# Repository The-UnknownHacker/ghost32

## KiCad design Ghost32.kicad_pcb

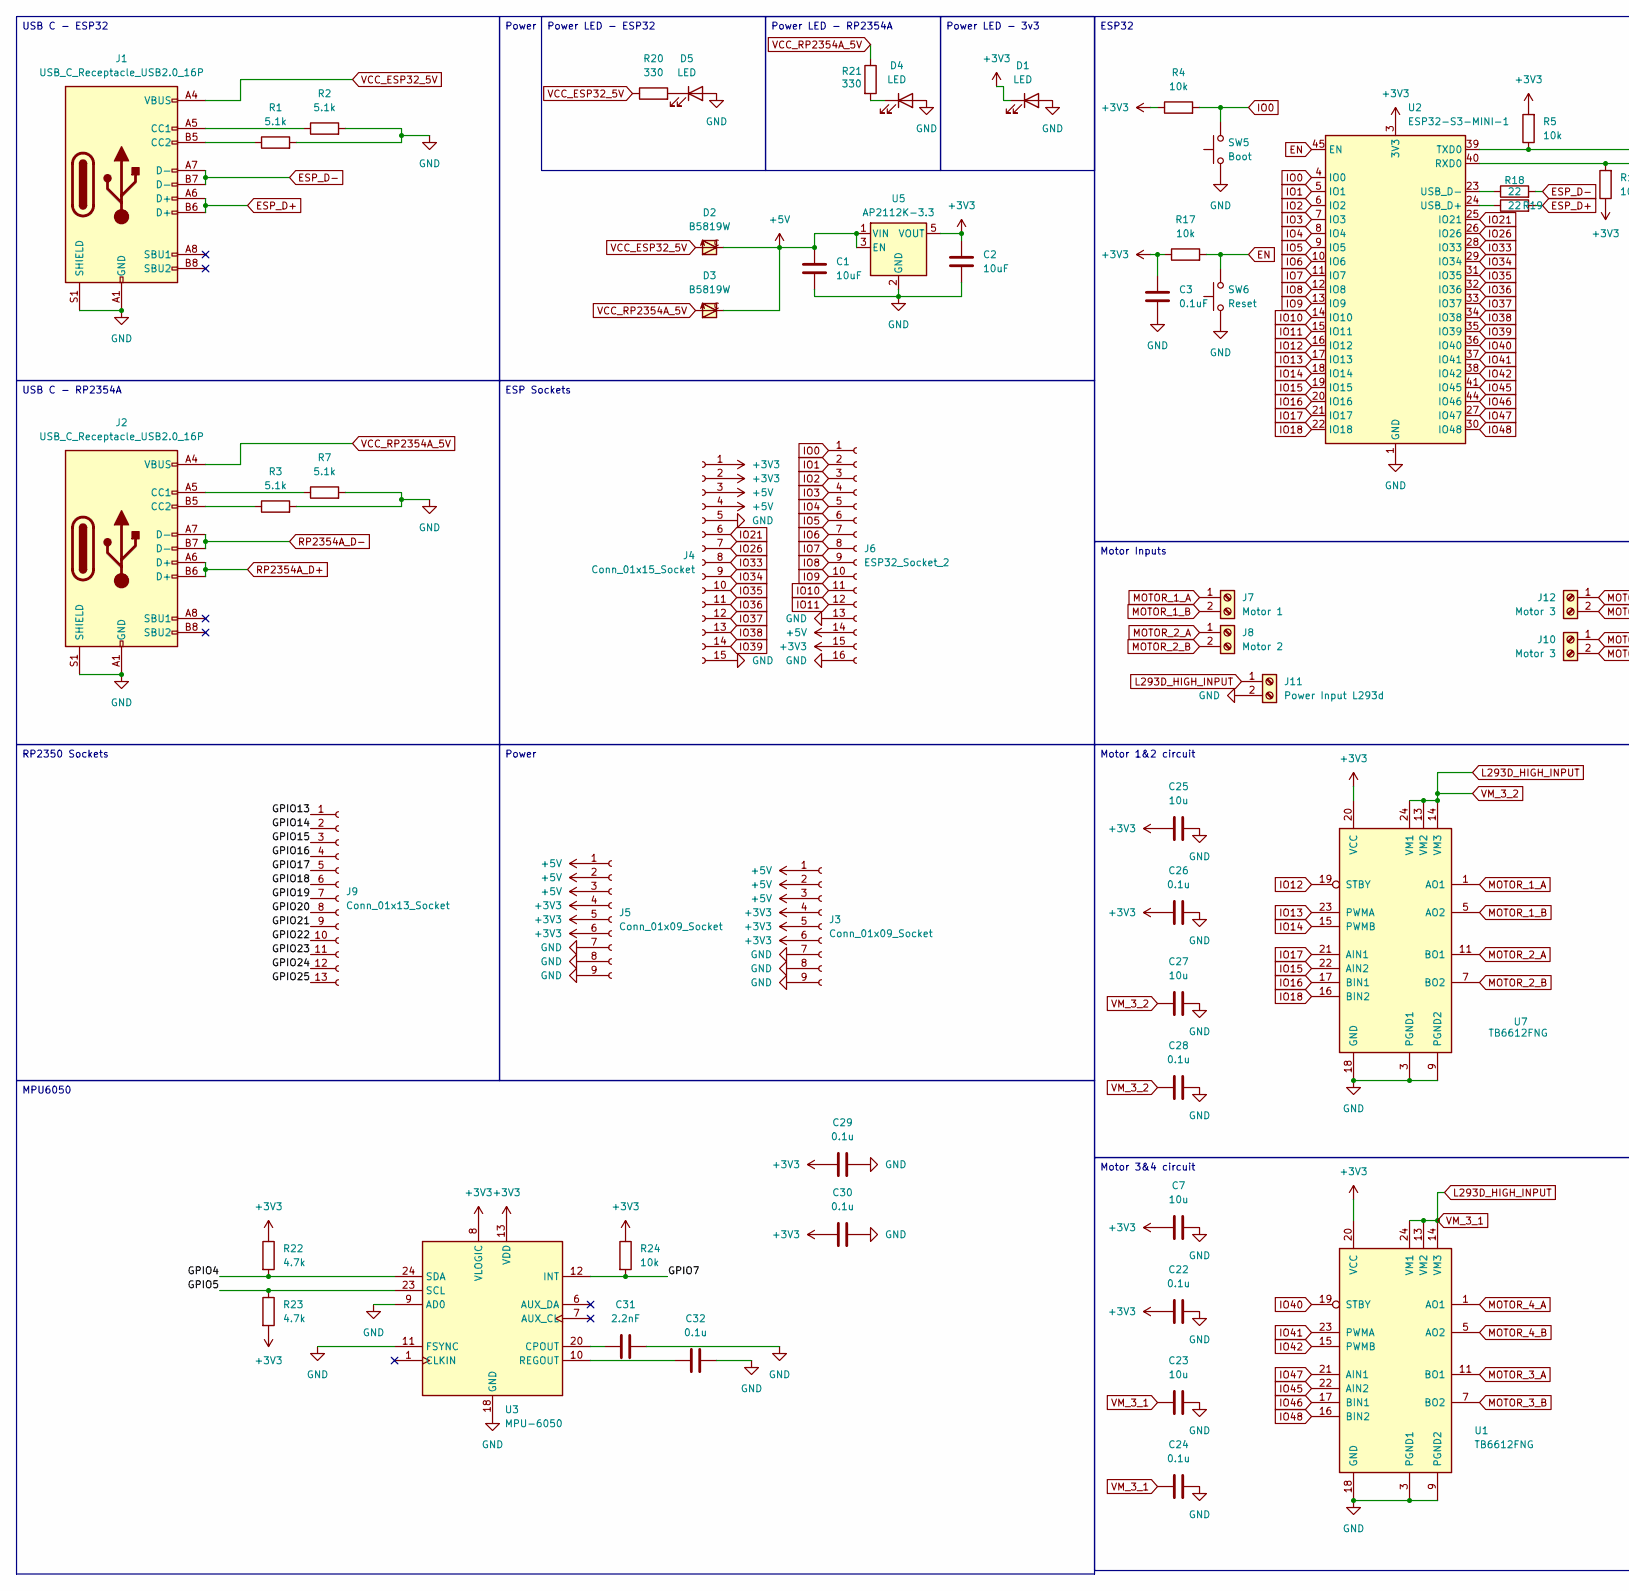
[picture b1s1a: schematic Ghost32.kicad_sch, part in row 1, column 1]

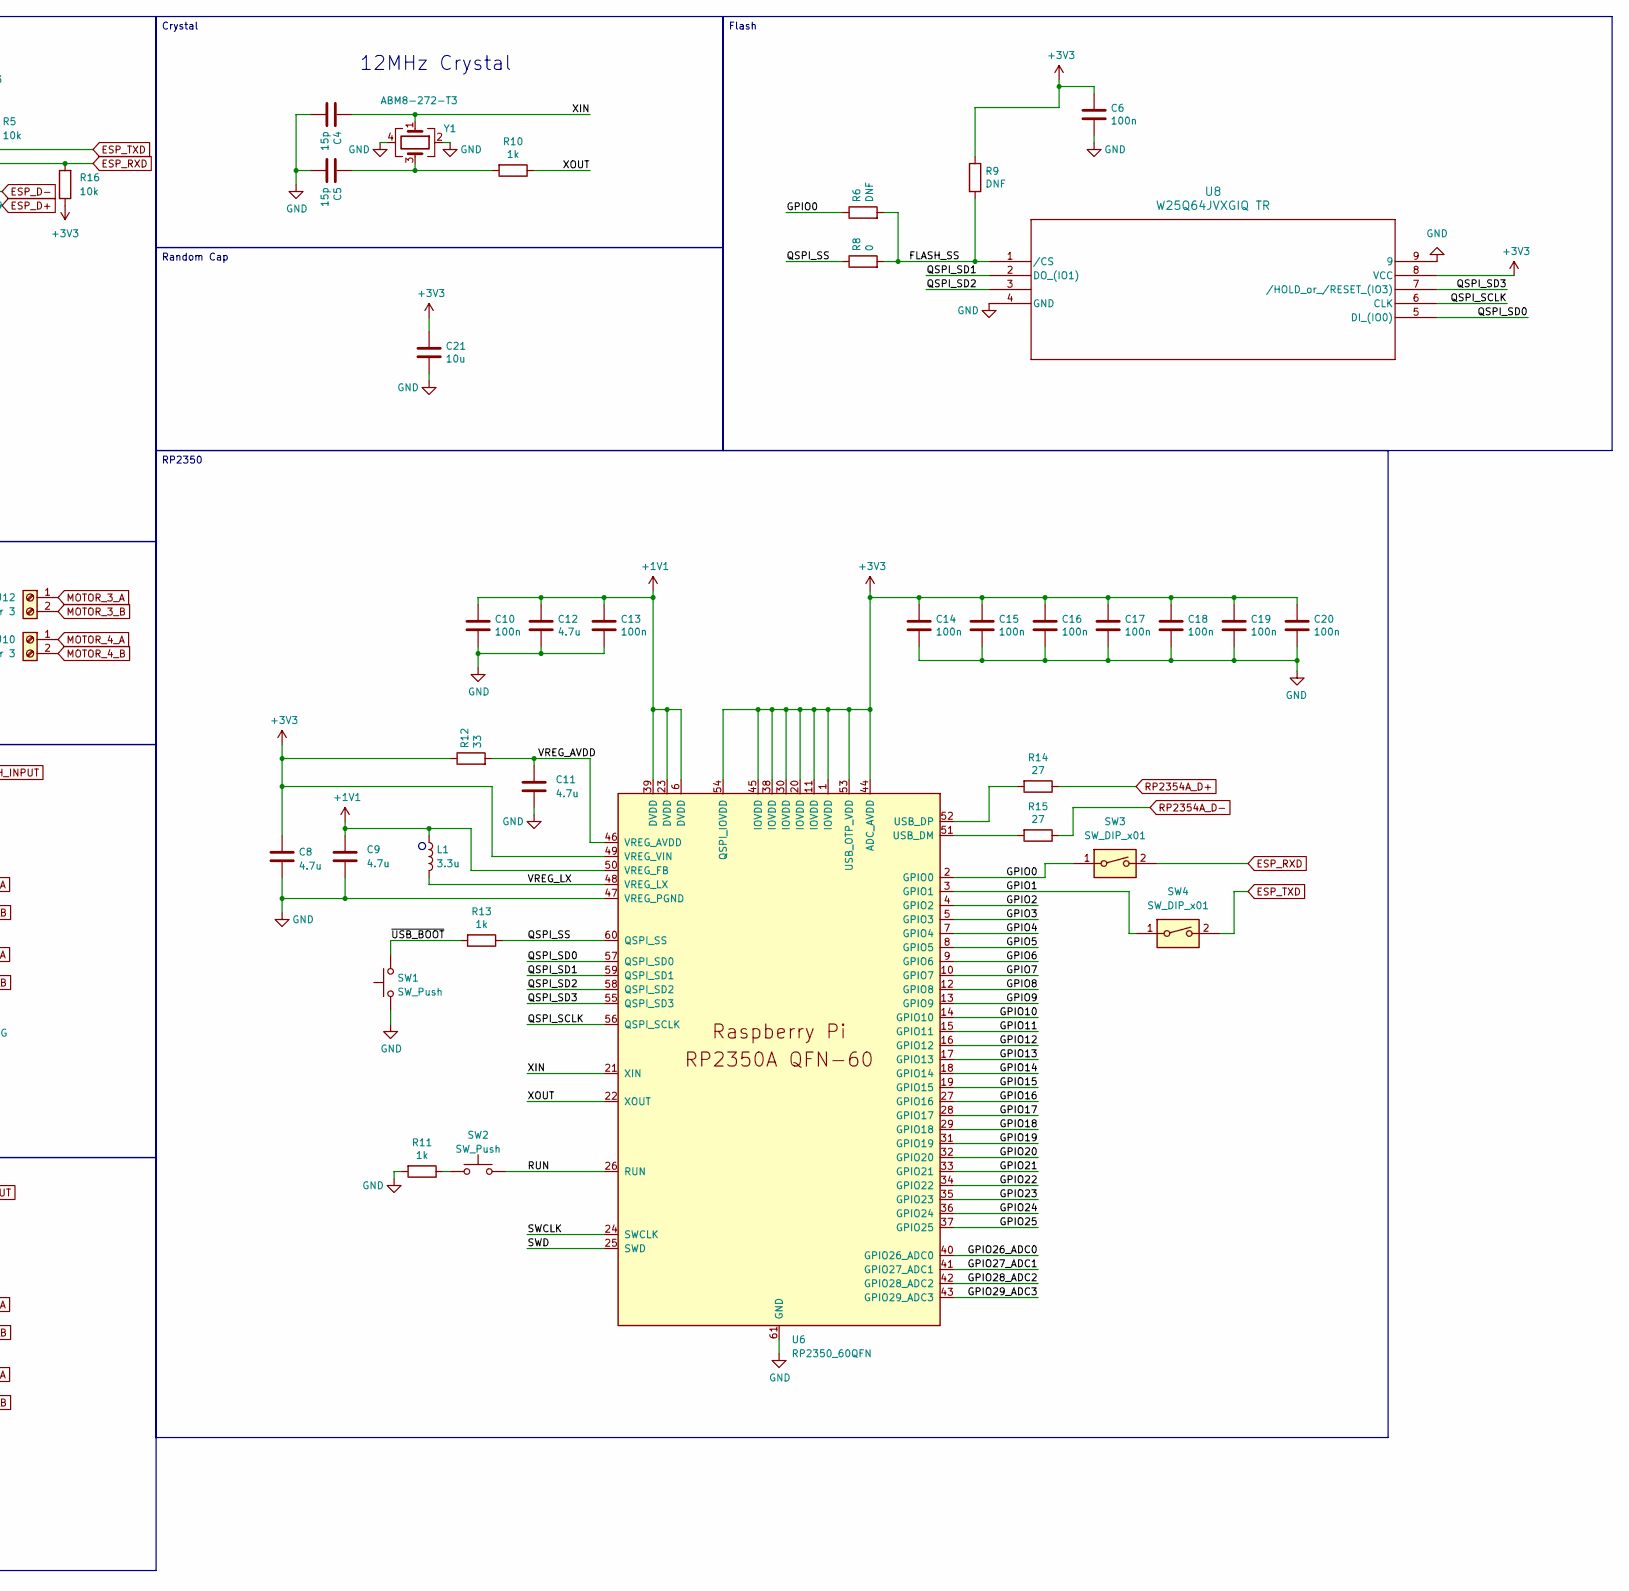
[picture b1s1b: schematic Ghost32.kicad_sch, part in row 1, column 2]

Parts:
C1, C2: 10uF; C_0402_1005Metric
C3: 0.1uF; C_0402_1005Metric
C4, C5: 15p; C_0402_1005Metric
C6, C10, C13, C14, C15, C16, C17, C18, C19, C20: 100n; C_0402_1005Metric
C7, C21, C23, C25, C27: 10u; C_0402_1005Metric
C8, C9, C11, C12: 4.7u; C_0402_1005Metric
C22, C24, C26, C28, C29, C30, C32: 0.1u; C_0402_1005Metric
C31: 2.2nF; C_0402_1005Metric
D1, D4, D5: LED; LED_0805_2012Metric
D2, D3: B5819W; SOD123FL
J1, J2: USB_C_Receptacle_USB2.0_16P; USB_C_Receptacle_HRO_TYPE-C-31-M-12
J3, J5: Conn_01x09_Socket; PinSocket_1x09_P2.54mm_Vertical
J4: Conn_01x15_Socket; PinSocket_1x15_P2.54mm_Vertical
J6: ESP32_Socket_2; PinSocket_1x16_P2.54mm_Vertical
J7: Motor 1; Altech_AK300_1x02_P5.00mm_45-Degree
J8: Motor 2; Altech_AK300_1x02_P5.00mm_45-Degree
J9: Conn_01x13_Socket; PinSocket_1x13_P2.54mm_Vertical
J10, J12: Motor 3; Altech_AK300_1x02_P5.00mm_45-Degree
J11: Power Input L293d; Altech_AK300_1x02_P5.00mm_45-Degree
L1: 3.3u; L_0805_2012Metric
R1, R2, R3, R7: 5.1k; R_0402_1005Metric
R4, R5, R16, R17, R24: 10k; R_0402_1005Metric
R6, R9: DNF; R_0402_1005Metric
R8: 0; R_0402_1005Metric
R10, R11, R13: 1k; R_0402_1005Metric
R12: 33; R_0402_1005Metric
R14, R15: 27; R_0402_1005Metric
R18, R19: 22; R_0402_1005Metric
R20, R21: 330; R_0402_1005Metric
R22, R23: 4.7k; R_0402_1005Metric
SW1, SW2: SW_Push; SW_Push_1P1T_NO_Vertical_Wuerth_434133025816
SW3, SW4: SW_DIP_x01; SW_DIP_SPSTx01_Slide_6.7x4.1mm_W6.73mm_P2.54mm_LowProfile_J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
SW5: Boot; SW_Push_1P1T_NO_Vertical_Wuerth_434133025816
SW6: Reset; SW_Push_1P1T_NO_Vertical_Wuerth_434133025816
U1, U7: TB6612FNG; SSOP-24_5.3x8.2mm_P0.65mm
U2: ESP32-S3-MINI-1; ESP32-S2-MINI-1
U3: MPU-6050; InvenSense_QFN-24_4x4mm_P0.5mm
U5: AP2112K-3.3; SOT-23-5
U6: RP2350_60QFN; QFN-60-1EP_7x7mm_P0.4mm_EP3.4x3.4mm
U8: W25Q64JVXGIQ TR; DFN_XGIQ TR_WIN
Y1: ABM8-272-T3; Crystal_SMD_3225-4Pin_3.2x2.5mm

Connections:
+1V1: C9.1, C10.1, C12.1, C13.1, L1.1, U6.6 (DVDD), U6.23 (DVDD), U6.39 (DVDD), U6.50 (VREG_FB)
+3V3: C2.1, C3.1, C6.1, C7.1, C8.1, C14.1, C15.1, C16.1, C17.1, C18.1, C19.1, C20.1, C21.1, C22.1, C25.1, C26.1, C29.1, C30.1, D1.1 (K), J3.4, J3.5, J3.6, J4.1, J4.2, J5.4, J5.5, J5.6, J6.15, R4.1, R5.2, R9.1, R12.1, R16.1, R17.1, R22.1, R23.2, R24.1, U1.20 (VCC), U2.3 (3V3), U3.8 (VLOGIC), U3.13 (VDD), U5.5 (VOUT), U6.1 (IOVDD), U6.11 (IOVDD), U6.20 (IOVDD), U6.30 (IOVDD), U6.38 (IOVDD), U6.44 (ADC_AVDD), U6.45 (IOVDD), U6.49 (VREG_VIN), U6.53 (USB_OTP_VDD), U6.54 (QSPI_IOVDD), U7.20 (VCC), U8.8 (VCC)
+5V: C1.1, D2.C, D3.C, J3.1, J3.2, J3.3, J4.3, J4.4, J5.1, J5.2, J5.3, J6.14, U5.1 (VIN), U5.3 (EN)
/FLASH_SS: R6.2, R8.2, R9.2, U8.1 (/CS)
/GPIO0: R6.1, SW3.1, U6.2 (GPIO0)
/GPIO1: SW4.1, U6.3 (GPIO1)
/GPIO2: U6.4 (GPIO2)
/GPIO3: U6.5 (GPIO3)
/GPIO4: R22.2, U3.24 (SDA), U6.7 (GPIO4)
/GPIO5: R23.1, U3.23 (SCL), U6.8 (GPIO5)
/GPIO6: U6.9 (GPIO6)
/GPIO7: R24.2, U3.12 (INT), U6.10 (GPIO7)
/GPIO8: U6.12 (GPIO8)
/GPIO9: U6.13 (GPIO9)
/GPIO10: U6.14 (GPIO10)
/GPIO11: U6.15 (GPIO11)
/GPIO12: U6.16 (GPIO12)
/GPIO13: J9.1, U6.17 (GPIO13)
/GPIO14: J9.2, U6.18 (GPIO14)
/GPIO15: J9.3, U6.19 (GPIO15)
/GPIO16: J9.4, U6.27 (GPIO16)
/GPIO17: J9.5, U6.28 (GPIO17)
/GPIO18: J9.6, U6.29 (GPIO18)
/GPIO19: J9.7, U6.31 (GPIO19)
/GPIO20: J9.8, U6.32 (GPIO20)
/GPIO21: J9.9, U6.33 (GPIO21)
/GPIO22: J9.10, U6.34 (GPIO22)
/GPIO23: J9.11, U6.35 (GPIO23)
/GPIO24: J9.12, U6.36 (GPIO24)
/GPIO25: J9.13, U6.37 (GPIO25)
/GPIO26_ADC0: U6.40 (GPIO26_ADC0)
/GPIO27_ADC1: U6.41 (GPIO27_ADC1)
/GPIO28_ADC2: U6.42 (GPIO28_ADC2)
/GPIO29_ADC3: U6.43 (GPIO29_ADC3)
/QSPI_SCLK: U6.56 (QSPI_SCLK), U8.6 (CLK)
/QSPI_SD0: U6.57 (QSPI_SD0), U8.5 (DI_(IO0))
/QSPI_SD1: U6.59 (QSPI_SD1), U8.2 (DO_(IO1))
/QSPI_SD2: U6.58 (QSPI_SD2), U8.3
/QSPI_SD3: U6.55 (QSPI_SD3), U8.7 (/HOLD_or_/RESET_(IO3))
/QSPI_SS: R8.1, R13.1, U6.60 (QSPI_SS)
/RUN: SW2.2, U6.26 (RUN)
/SWCLK: U6.24 (SWCLK)
/SWD: U6.25 (SWD)
/VREG_AVDD: C11.1, R12.2, U6.46 (VREG_AVDD)
/VREG_LX: L1.2, U6.48 (VREG_LX)
/XIN: C4.1, U6.21 (XIN), Y1.1
/XOUT: R10.1, U6.22 (XOUT)
/~USB_BOOT: R13.2, SW1.2
EN: R17.2, SW6.2, U2.45 (EN)
ESP_D+: J1.A6 (D+), J1.B6 (D+), R19.2
ESP_D-: J1.A7 (D-), J1.B7 (D-), R18.2
ESP_RXD: R16.2, SW3.2, U2.40 (RXD0)
ESP_TXD: R5.1, SW4.2, U2.39 (TXD0)
GND: C1.2, C2.2, C3.2, C4.2, C5.2, C6.2, C7.2, C8.2, C9.2, C10.2, C11.2, C12.2, C13.2, C14.2, C15.2, C16.2, C17.2, C18.2, C19.2, C20.2, C21.2, C22.2, C23.2, C24.2, C25.2, C26.2, C27.2, C28.2, C29.2, C30.2, C31.2, C32.2, D1.2 (A), D4.2 (A), D5.2 (A), J1.A1 (GND), J1.A12 (GND), J1.B1 (GND), J1.B12 (GND), J1.S1 (SHIELD), J2.A1 (GND), J2.A12 (GND), J2.B1 (GND), J2.B12 (GND), J2.S1 (SHIELD), J3.7, J3.8, J3.9, J4.5, J4.15, J5.7, J5.8, J5.9, J6.13, J6.16, J11.2, R1.2, R2.2, R3.2, R7.2, R11.2, SW1.1, SW5.1, SW6.1, U1.3 (PGND1), U1.4 (PGND1), U1.9 (PGND2), U1.10 (PGND2), U1.18 (GND), U2.1 (GND), U2.2 (GND), U2.42 (GND), U2.43 (GND), U2.46 (GND), U2.47 (GND), U2.48 (GND), U2.49 (GND), U2.50 (GND), U2.51 (GND), U2.52 (GND), U2.53 (GND), U2.54 (GND), U2.55 (GND), U2.56 (GND), U2.57 (GND), U2.58 (GND), U2.59 (GND), U2.60 (GND), U2.61 (GND), U2.62 (GND), U2.63 (GND), U2.64 (GND), U2.65 (GND), U3.9 (AD0), U3.11 (FSYNC), U3.18 (GND), U5.2 (GND), U6.47 (VREG_PGND), U6.61 (GND), U7.3 (PGND1), U7.4 (PGND1), U7.9 (PGND2), U7.10 (PGND2), U7.18 (GND), U8.4 (GND), U8.9, Y1.2, Y1.4
IO0: J6.1, R4.2, SW5.2, U2.4 (IO0)
IO1: J6.2, U2.5 (IO1)
IO2: J6.3, U2.6 (IO2)
IO3: J6.4, U2.7 (IO3)
IO4: J6.5, U2.8 (IO4)
IO5: J6.6, U2.9 (IO5)
IO6: J6.7, U2.10 (IO6)
IO7: J6.8, U2.11 (IO7)
IO8: J6.9, U2.12 (IO8)
IO9: J6.10, U2.13 (IO9)
IO10: J6.11, U2.14 (IO10)
IO11: J6.12, U2.15 (IO11)
IO12: U2.16 (IO12), U7.19 (STBY)
IO13: U2.17 (IO13), U7.23 (PWMA)
IO14: U2.18 (IO14), U7.15 (PWMB)
IO15: U2.19 (IO15), U7.22 (AIN2)
IO16: U2.20 (IO16), U7.17 (BIN1)
IO17: U2.21 (IO17), U7.21 (AIN1)
IO18: U2.22 (IO18), U7.16 (BIN2)
IO21: J4.6, U2.25 (IO21)
IO26: J4.7, U2.26 (IO26)
IO33: J4.8, U2.28 (IO33)
IO34: J4.9, U2.29 (IO34)
IO35: J4.10, U2.31 (IO35)
IO36: J4.11, U2.32 (IO36)
IO37: J4.12, U2.33 (IO37)
IO38: J4.13, U2.34 (IO38)
IO39: J4.14, U2.35 (IO39)
IO40: U1.19 (STBY), U2.36 (IO40)
IO41: U1.23 (PWMA), U2.37 (IO41)
IO42: U1.15 (PWMB), U2.38 (IO42)
IO45: U1.22 (AIN2), U2.41 (IO45)
IO46: U1.17 (BIN1), U2.44 (IO46)
IO47: U1.21 (AIN1), U2.27 (IO47)
IO48: U1.16 (BIN2), U2.30 (IO48)
L293D_HIGH_INPUT: C23.1, C24.1, C27.1, C28.1, J11.1, U1.13 (VM2), U1.14 (VM3), U1.24 (VM1), U7.13 (VM2), U7.14 (VM3), U7.24 (VM1)
MOTOR_1_A: J7.1, U7.1 (AO1), U7.2 (AO1)
MOTOR_1_B: J7.2, U7.5 (AO2), U7.6 (AO2)
MOTOR_2_A: J8.1, U7.11 (BO1), U7.12 (BO1)
MOTOR_2_B: J8.2, U7.7 (BO2), U7.8 (BO2)
MOTOR_3_A: J12.1, U1.11 (BO1), U1.12 (BO1)
MOTOR_3_B: J12.2, U1.7 (BO2), U1.8 (BO2)
MOTOR_4_A: J10.1, U1.1 (AO1), U1.2 (AO1)
MOTOR_4_B: J10.2, U1.5 (AO2), U1.6 (AO2)
unnamed: C5.1, R10.2, Y1.3
unnamed: D4.1 (K), R21.2
unnamed: D5.1 (K), R20.2
unnamed: J1.A5 (CC1), R2.1
unnamed: J1.B5 (CC2), R1.1
unnamed: J2.A5 (CC1), R7.1
unnamed: J2.B5 (CC2), R3.1
unnamed: R11.1, SW2.1
unnamed: R19.1, U2.24 (USB_D+)
unnamed: R18.1, U2.23 (USB_D-)
unnamed: C31.1, U3.20 (CPOUT)
unnamed: C32.1, U3.10 (REGOUT)
unnamed: R15.2, U6.51 (USB_DM)
unnamed: R14.2, U6.52 (USB_DP)
RP2354A_D+: J2.A6 (D+), J2.B6 (D+), R14.1
RP2354A_D-: J2.A7 (D-), J2.B7 (D-), R15.1
VCC_ESP32_5V: D2.A, J1.A4 (VBUS), J1.A9 (VBUS), J1.B4 (VBUS), J1.B9 (VBUS), R20.1
VCC_RP2354A_5V: D3.A, J2.A4 (VBUS), J2.A9 (VBUS), J2.B4 (VBUS), J2.B9 (VBUS), R21.1

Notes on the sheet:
12MHz Crystal
Motor Inputs
ESP32
Power LED - RP2354A
Flash
Power
USB C - ESP32
Power
Power LED - ESP32
Random Cap
Crystal
Power LED - 3v3
MPU6050
ESP Sockets
RP2350 Sockets
Motor 1&2 circuit
USB C - RP2354A
RP2350
Motor 3&4 circuit

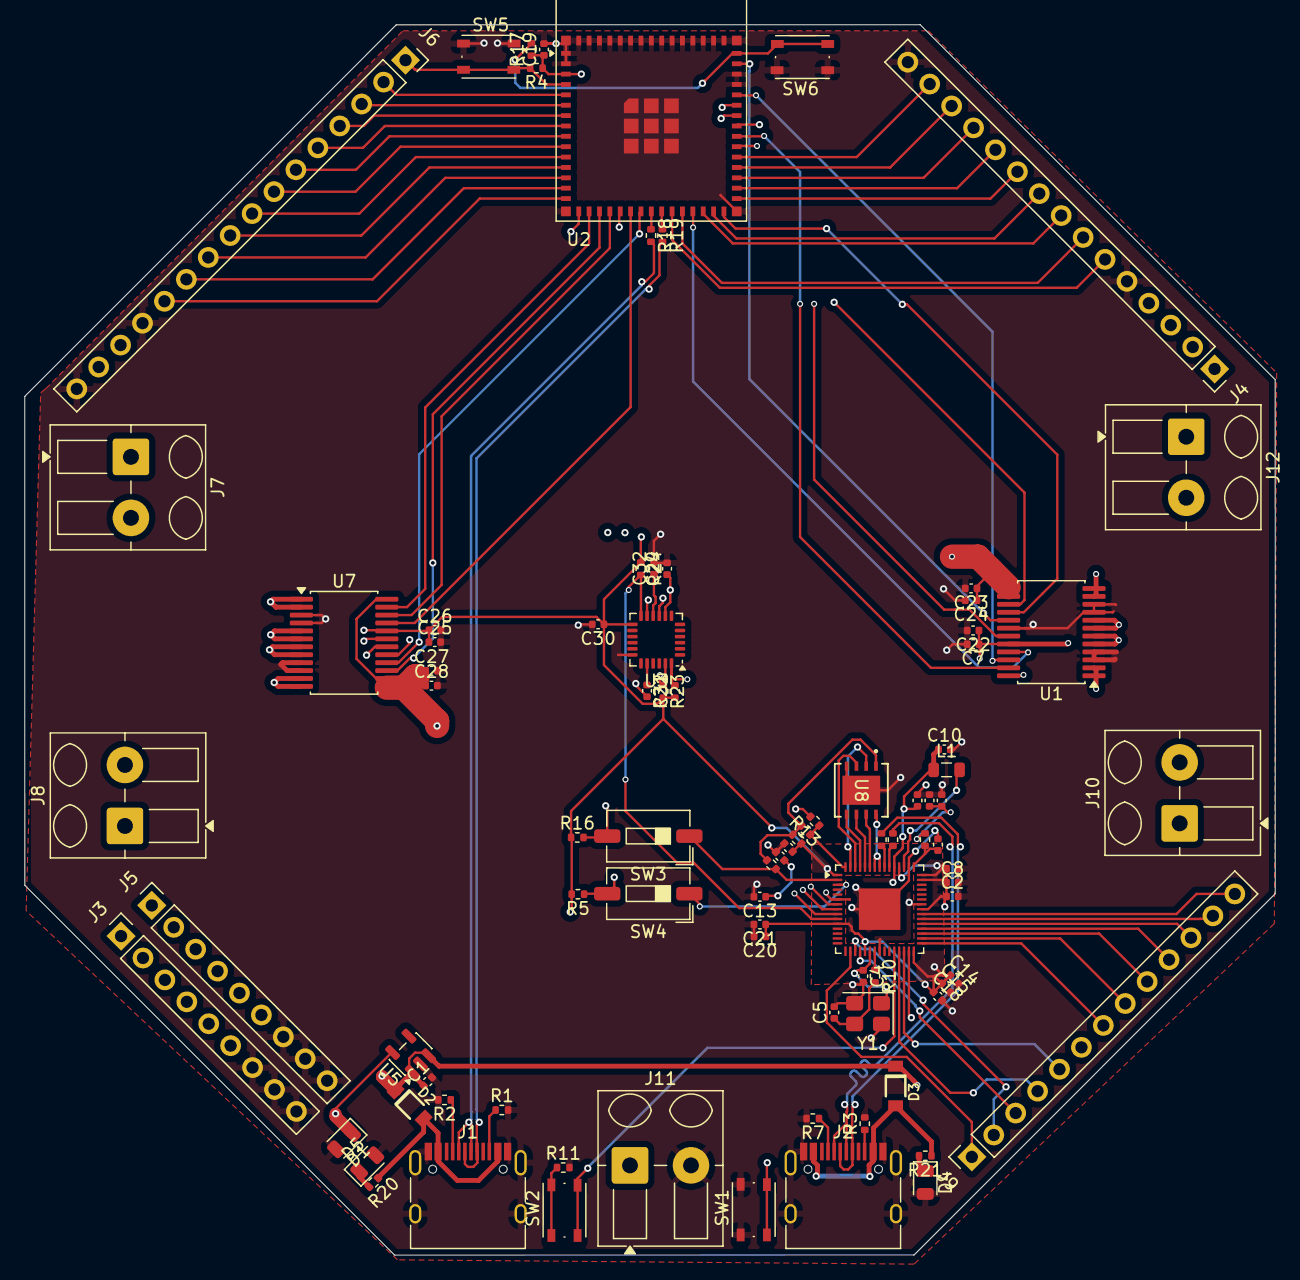
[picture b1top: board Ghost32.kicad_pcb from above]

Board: 4 copper layers, 102.5 x 100.8 mm, 88 parts (0 on the bottom side), 102 nets.

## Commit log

2025-11-18 Add files
